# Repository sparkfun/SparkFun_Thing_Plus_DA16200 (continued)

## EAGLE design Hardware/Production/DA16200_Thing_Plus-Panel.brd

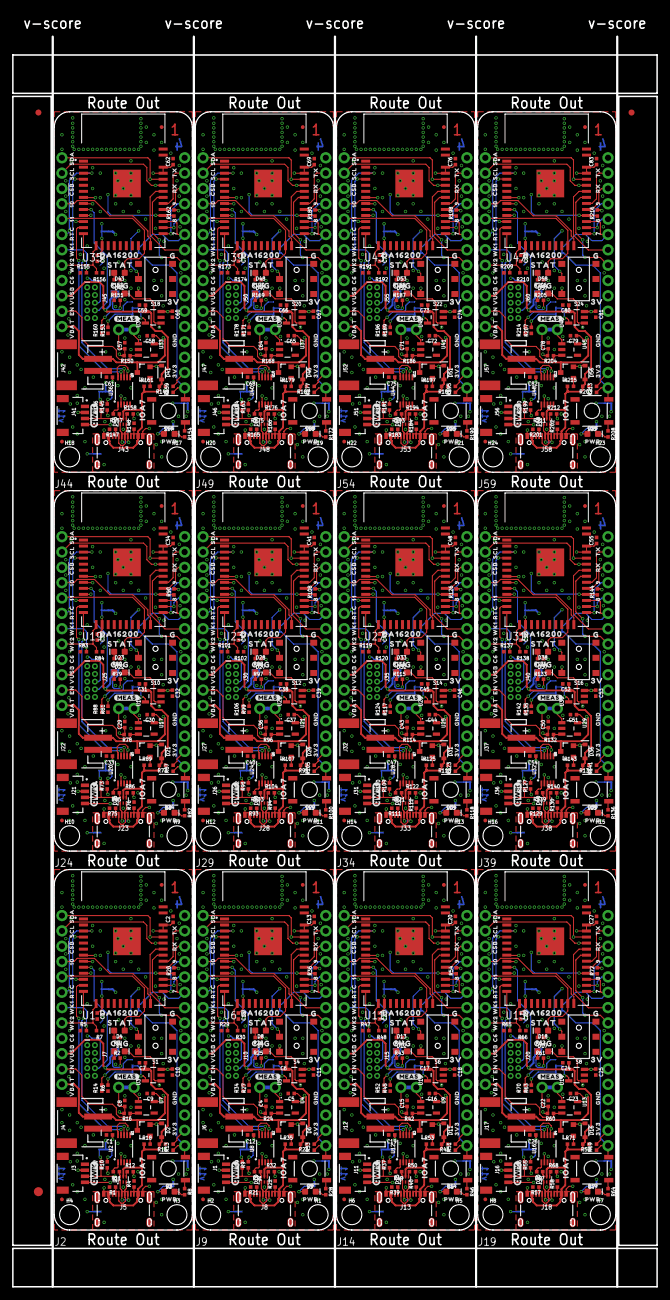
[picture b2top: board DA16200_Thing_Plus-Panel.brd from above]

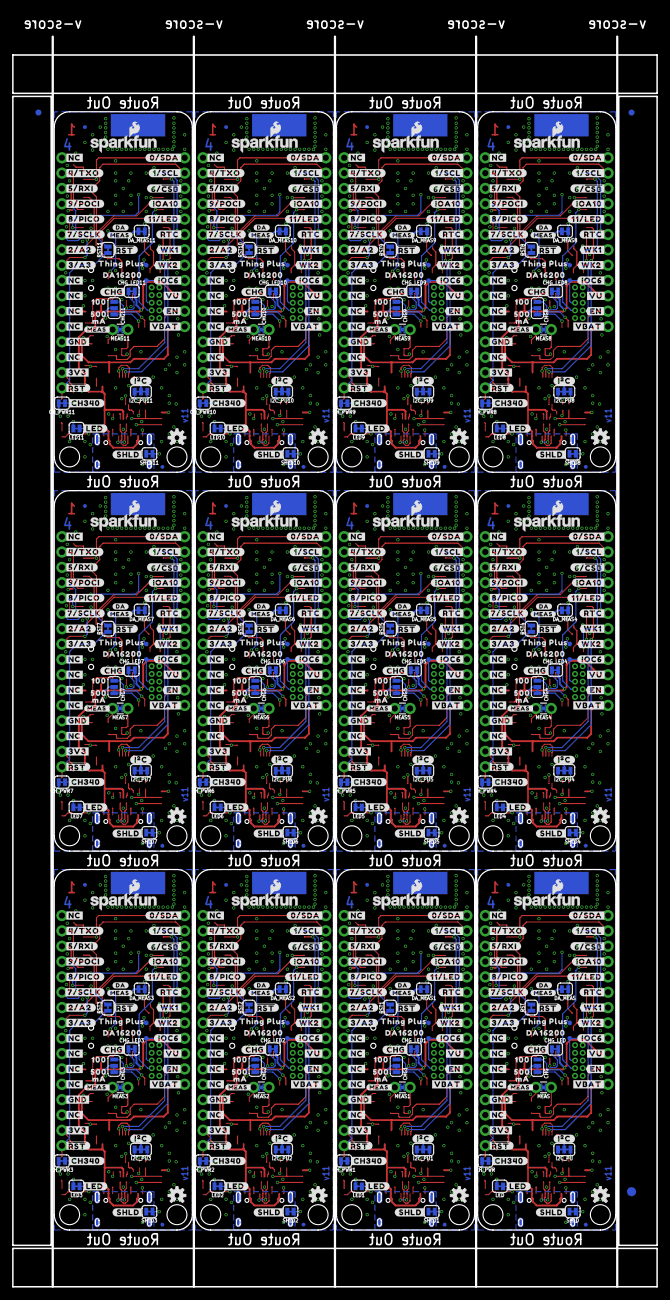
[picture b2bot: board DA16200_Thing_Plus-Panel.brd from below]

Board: 4 copper layers, 106.7 x 207.0 mm, 1578 parts (687 on the bottom side), 636 nets.

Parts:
C1, C2, C3, C12, C13, C14, C19, C20, C21, C26, C27, C28, C33, C34, C35, C40, C41, C42, C47, C48, C49, C54, C55, C56, C61, C62, C63, C68, C69, C70, C75, C76, C77, C82, C83, C84: 0.1uF; 0402-TIGHT
C4, C8, C15, C22, C29, C36, C43, C50, C57, C64, C71, C78: 1.0uF; 0402-TIGHT
C5, C9, C16, C23, C30, C37, C44, C51, C58, C65, C72, C79: 2.2uF; 0402-TIGHT
C6, C7, C10, C11, C17, C18, C24, C25, C31, C32, C38, C39, C45, C46, C52, C53, C59, C60, C66, C67, C73, C74, C80, C81: 4.7uF; 0402-TIGHT
CHG, CHG1, CHG2, CHG3, CHG4, CHG5, CHG6, CHG7, CHG8, CHG9, CHG10, CHG11: JUMPER-SMT_3_1-NC_TRACE_SILK; SMT-JUMPER_3_1-NC_TRACE_SILK
CHG_LED, CHG_LED1, CHG_LED2, CHG_LED3, CHG_LED4, CHG_LED5, CHG_LED6, CHG_LED7, CHG_LED8, CHG_LED9, CHG_LED10, CHG_LED11: JUMPER-SMT_2_NC_TRACE_SILK; SMT-JUMPER_2_NC_TRACE_SILK
CH_PWR, CH_PWR1, CH_PWR2, CH_PWR3, CH_PWR4, CH_PWR5, CH_PWR6, CH_PWR7, CH_PWR8, CH_PWR9, CH_PWR10, CH_PWR11: JUMPER-SMT_2_NC_TRACE_SILK; SMT-JUMPER_2_NC_TRACE_SILK
D1, D7, D12, D17, D22, D27, D32, D37, D42, D47, D52, D57: Yellow; LED-0603
D2, D6, D11, D16, D21, D26, D31, D36, D41, D46, D51, D56: 1A/23V/620mV; SOD-323
D3, D9, D14, D19, D24, D29, D34, D39, D44, D49, D54, D59: RED; LED-0603
D4, D8, D13, D18, D23, D28, D33, D38, D43, D48, D53, D58: BLUE; LED-0603
D5, D10, D15, D20, D25, D30, D35, D40, D45, D50, D55, D60: PRTR5V0U2F; SOT886
DA_MEAS, DA_MEAS1, DA_MEAS2, DA_MEAS3, DA_MEAS4, DA_MEAS5, DA_MEAS6, DA_MEAS7, DA_MEAS8, DA_MEAS9, DA_MEAS10, DA_MEAS11: JUMPER-SMT_2_NC_TRACE_SILK; SMT-JUMPER_2_NC_TRACE_SILK
E$1, E$2, E$3, E$4: FIDUCIAL-1X2
E$5, E$6: FIDUCIAL-1.5X3
FD1, FD2, FD3, FD4, FD5, FD6, FD7, FD8, FD9, FD10, FD11, FD12, FD13, FD14, FD15, FD16, FD17, FD18, FD19, FD20, FD21, FD22, FD23, FD24, FD25, FD26, FD27, FD28, FD29, FD30, FD31, FD32, FD33, FD34, FD35, FD36, FD37, FD38, FD39, FD40, FD41, FD42, FD43, FD44, FD45, FD46, FD47, FD48: FIDUCIALUFIDUCIAL; FIDUCIAL-MICRO
GPIOC1, GPIOC2, GPIOC3, GPIOC4, GPIOC5, GPIOC6, GPIOC7, GPIOC8, GPIOC9, GPIOC10, GPIOC11, GPIOC12: TEST-POINT3; PAD.03X.03
H1, H2, H3, H4, H5, H6, H7, H8, H9, H10, H11, H12, H13, H14, H15, H16, H17, H18, H19, H20, H21, H22, H23, H24: STAND-OFF
I2C_PU, I2C_PU1, I2C_PU2, I2C_PU3, I2C_PU4, I2C_PU5, I2C_PU6, I2C_PU7, I2C_PU8, I2C_PU9, I2C_PU10, I2C_PU11: JUMPER-SMT_3_2-NC_TRACE_SILK; SMT-JUMPER_3_2-NC_TRACE_SILK
J1, J3, J11, J16, J21, J26, J31, J36, J41, J46, J51, J56: Qwiic; JST04_1MM_RA
J2, J9, J14, J19, J24, J29, J34, J39, J44, J49, J54, J59: THING_PLUS
J4, J6, J12, J17, J22, J27, J32, J37, J42, J47, J52, J57: JST-2-SMD
J5, J8, J13, J18, J23, J28, J33, J38, J43, J48, J53, J58: USB C; USB-C-16P-4LAYER-ISOLATED
J7, J10, J15, J20, J25, J30, J35, J40, J45, J50, J55, J60: CORTEX_JTAG_DEBUG_PTH_NS; 2X5-PTH-1.27MM-NO_SILK
LED, LED1, LED2, LED3, LED4, LED5, LED6, LED7, LED8, LED9, LED10, LED11: JUMPER-SMT_2_NC_TRACE_SILK; SMT-JUMPER_2_NC_TRACE_SILK
LOGO1, LOGO3, LOGO5, LOGO7, LOGO9, LOGO11, LOGO13, LOGO15, LOGO17, LOGO19, LOGO21, LOGO23: OSHW-LOGOS; OSHW-LOGO-S
LOGO2, LOGO4, LOGO6, LOGO8, LOGO10, LOGO12, LOGO14, LOGO16, LOGO18, LOGO20, LOGO22, LOGO24: SFE_LOGO_NAME_FLAME.1_INCH; SFE_LOGO_NAME_FLAME_.1
MEAS, MEAS1, MEAS2, MEAS3, MEAS4, MEAS5, MEAS6, MEAS7, MEAS8, MEAS9, MEAS10, MEAS11: JUMPER-COMBO_2_NC_TRACE; COMBO-JUMPER_2_NC_TRACE
Q1, Q2, Q3, Q4, Q5, Q6, Q7, Q8, Q9, Q10, Q11, Q12: 20V/4.2A/52mΩ/1.4W; SOT23-3
R1, R4, R21, R22, R39, R40, R57, R58, R75, R76, R93, R94, R111, R112, R129, R130, R147, R148, R165, R166, R183, R184, R201, R202: 5.1k; 0402-TIGHT
R2, R3, R8, R25, R26, R28, R43, R44, R46, R61, R62, R64, R79, R80, R82, R97, R98, R100, R115, R116, R118, R133, R134, R136, R151, R152, R154, R169, R170, R172, R187, R188, R190, R205, R206, R208: 1k; 0402-TIGHT
R5, R7, R29, R30, R47, R48, R65, R66, R83, R84, R101, R102, R119, R120, R137, R138, R155, R156, R173, R174, R191, R192, R209, R210: 4.7k; 0402-TIGHT
R6, R27, R45, R63, R81, R99, R117, R135, R153, R171, R189, R207: 2.0K; 0402-TIGHT
R9, R10, R17, R19, R37, R38, R55, R56, R73, R74, R91, R92, R109, R110, R127, R128, R145, R146, R163, R164, R181, R182, R199, R200: 2.2k; 0402-TIGHT
R11, R12, R31, R32, R49, R50, R67, R68, R85, R86, R103, R104, R121, R122, R139, R140, R157, R158, R175, R176, R193, R194, R211, R212: 27; 0402-TIGHT
R13, R14, R15, R16, R20, R23, R24, R33, R34, R36, R41, R42, R51, R52, R54, R59, R60, R69, R70, R72, R77, R78, R87, R88, R90, R95, R96, R105, R106, R108, R113, R114, R123, R124, R126, R131, R132, R141, R142, R144, R149, R150, R159, R160, R162, R167, R168, R177, R178, R180, R185, R186, R195, R196, R198, R203, R204, R213, R214, R216: 10k; 0402-TIGHT
R18, R35, R53, R71, R89, R107, R125, R143, R161, R179, R197, R215: 100; 0402-TIGHT
RST, RST1, RST2, RST3, RST4, RST5, RST6, RST7, RST8, RST9, RST10, RST11: JUMPER-SMT_2_NC_TRACE_SILK; SMT-JUMPER_2_NC_TRACE_SILK
S1, S4, S6, S8, S10, S12, S14, S16, S18, S20, S22, S24: SWITCH_DPDT_SMD_AYZ0202
S2, S3, S5, S7, S9, S11, S13, S15, S17, S19, S21, S23: MOMENTARY-SWITCH-SPST-SMD-5.2MM-TALL; TACTILE_SWITCH_SMD_5.2MM
SHLD, SHLD1, SHLD2, SHLD3, SHLD4, SHLD5, SHLD6, SHLD7, SHLD8, SHLD9, SHLD10, SHLD11: JUMPER-SMT_2_NC_TRACE_SILK; SMT-JUMPER_2_NC_TRACE_SILK
TMS, TMS1, TMS2, TMS3, TMS4, TMS5, TMS6, TMS7, TMS8, TMS9, TMS10, TMS11: TEST-POINT3; PAD.03X.03
U1, U6, U11, U15, U19, U23, U27, U31, U35, U39, U43, U47: DA16200MOD; XCVR_DA16200MOD-AAC4WA32
U2, U8, U12, U16, U20, U24, U28, U32, U36, U40, U44, U48: CH340E_MSOP10; MSOP10
U3, U5, U10, U14, U18, U22, U26, U30, U34, U38, U42, U46: MCP73831; SOT23-5
U4, U7, U9, U13, U17, U21, U25, U29, U33, U37, U41, U45: XC6222B331MR-G; SOT23-5
U$1, U$86, U$156, U$226, U$296, U$366, U$436, U$506, U$576, U$646, U$716, U$786: STAT0
U$2, U$87, U$157, U$227, U$297, U$367, U$437, U$507, U$577, U$647, U$717, U$787: CHG0
U$3, U$90, U$160, U$230, U$300, U$370, U$440, U$510, U$580, U$650, U$720, U$790: #MEAS_#0
U$4, U$91, U$161, U$231, U$301, U$371, U$441, U$511, U$581, U$651, U$721, U$791: G0
U$5, U$43, U$88, U$140, U$158, U$210, U$228, U$280, U$298, U$350, U$368, U$420, U$438, U$490, U$508, U$560, U$578, U$630, U$648, U$700, U$718, U$770, U$788, U$840: ##RST##0
U$6, U$94, U$164, U$234, U$304, U$374, U$444, U$514, U$584, U$654, U$724, U$794: #VU#0
U$7, U$129, U$199, U$269, U$339, U$409, U$479, U$549, U$619, U$689, U$759, U$829: #IOA10#0
U$8, U$29, U$89, U$138, U$159, U$208, U$229, U$278, U$299, U$348, U$369, U$418, U$439, U$488, U$509, U$558, U$579, U$628, U$649, U$698, U$719, U$768, U$789, U$838: #MEAS#0
U$9, U$92, U$162, U$232, U$302, U$372, U$442, U$512, U$582, U$652, U$722, U$792: 3V0
U$10, U$123, U$193, U$263, U$333, U$403, U$473, U$543, U$613, U$683, U$753, U$823: #CH340#0
U$11, U$124, U$194, U$264, U$334, U$404, U$474, U$544, U$614, U$684, U$754, U$824: #0#SDA#0
U$12, U$125, U$195, U$265, U$335, U$405, U$475, U$545, U$615, U$685, U$755, U$825: #1#SCL#0
U$13, U$93, U$163, U$233, U$303, U$373, U$443, U$513, U$583, U$653, U$723, U$793: IOA7_0
U$14, U$15, U$18, U$19, U$20, U$40, U$95, U$96, U$97, U$98, U$99, U$114, U$165, U$166, U$167, U$168, U$169, U$184, U$235, U$236, U$237, U$238, U$239, U$254, U$305, U$306, U$307, U$308, U$309, U$324, U$375, U$376, U$377, U$378, U$379, U$394, U$445, U$446, U$447, U$448, U$449, U$464, U$515, U$516, U$517, U$518, U$519, U$534, U$585, U$586, U$587, U$588, U$589, U$604, U$655, U$656, U$657, U$658, U$659, U$674, U$725, U$726, U$727, U$728, U$729, U$744, U$795, U$796, U$797, U$798, U$799, U$814: #NC#0
U$16, U$46, U$142, U$212, U$282, U$352, U$422, U$492, U$562, U$632, U$702, U$772: PWR0
U$17, U$137, U$207, U$277, U$347, U$417, U$487, U$557, U$627, U$697, U$767, U$837: #DA#0
U$21, U$100, U$170, U$240, U$310, U$380, U$450, U$520, U$590, U$660, U$730, U$800: 5000
U$22, U$101, U$171, U$241, U$311, U$381, U$451, U$521, U$591, U$661, U$731, U$801: 1000
U$23, U$102, U$172, U$242, U$312, U$382, U$452, U$522, U$592, U$662, U$732, U$802: MA0
U$24, U$103, U$173, U$243, U$313, U$383, U$453, U$523, U$593, U$663, U$733, U$803: SDA0
U$25, U$104, U$174, U$244, U$314, U$384, U$454, U$524, U$594, U$664, U$734, U$804: SCL0
U$26, U$105, U$175, U$245, U$315, U$385, U$455, U$525, U$595, U$665, U$735, U$805: #CSB#0
U$27, U$130, U$200, U$270, U$340, U$410, U$480, U$550, U$620, U$690, U$760, U$830: #4#TXO#0
U$28, U$113, U$183, U$253, U$323, U$393, U$463, U$533, U$603, U$673, U$743, U$813: 110
U$30, U$139, U$209, U$279, U$349, U$419, U$489, U$559, U$629, U$699, U$769, U$839: #VBAT#0
U$31, U$64, U$141, U$211, U$281, U$351, U$421, U$491, U$561, U$631, U$701, U$771: QWIIC_4MM
U$32, U$106, U$176, U$246, U$316, U$386, U$456, U$526, U$596, U$666, U$736, U$806: 100
U$33, U$107, U$177, U$247, U$317, U$387, U$457, U$527, U$597, U$667, U$737, U$807: RTC0
U$34, U$108, U$178, U$248, U$318, U$388, U$458, U$528, U$598, U$668, U$738, U$808: WK10
U$35, U$109, U$179, U$249, U$319, U$389, U$459, U$529, U$599, U$669, U$739, U$809: WK20
U$36, U$131, U$201, U$271, U$341, U$411, U$481, U$551, U$621, U$691, U$761, U$831: #5#RXI#0
U$37, U$110, U$180, U$250, U$320, U$390, U$460, U$530, U$600, U$670, U$740, U$810: EN0
U$38, U$111, U$181, U$251, U$321, U$391, U$461, U$531, U$601, U$671, U$741, U$811: VUSB0
U$39, U$112, U$182, U$252, U$322, U$392, U$462, U$532, U$602, U$672, U$742, U$812: VBAT0
U$41, U$115, U$185, U$255, U$325, U$395, U$465, U$535, U$605, U$675, U$745, U$815: TX0
U$42, U$116, U$186, U$256, U$326, U$396, U$466, U$536, U$606, U$676, U$746, U$816: RX0
U$44, U$117, U$187, U$257, U$327, U$397, U$467, U$537, U$607, U$677, U$747, U$817: 90
U$45, U$118, U$188, U$258, U$328, U$398, U$468, U$538, U$608, U$678, U$748, U$818: 80
U$47, U$119, U$189, U$259, U$329, U$399, U$469, U$539, U$609, U$679, U$749, U$819: 70
U$48, U$50, U$143, U$213, U$283, U$353, U$423, U$493, U$563, U$633, U$703, U$773: #GND#0
U$49, U$51, U$144, U$214, U$284, U$354, U$424, U$494, U$564, U$634, U$704, U$774: #3V3#0
U$52, U$53, U$145, U$215, U$285, U$355, U$425, U$495, U$565, U$635, U$705, U$775: #EN#0
U$54, U$60, U$146, U$216, U$286, U$356, U$426, U$496, U$566, U$636, U$706, U$776: #IOC6#0
U$55, U$120, U$190, U$260, U$330, U$400, U$470, U$540, U$610, U$680, U$750, U$820: GND0
U$56, U$75, U$150, U$220, U$290, U$360, U$430, U$500, U$570, U$640, U$710, U$780: THING_PLUS0
U$57, U$121, U$191, U$261, U$331, U$401, U$471, U$541, U$611, U$681, U$751, U$821: 3V30
U$58, U$71, U$147, U$217, U$287, U$357, U$427, U$497, U$567, U$637, U$707, U$777: #WK2#0
U$59, U$122, U$192, U$262, U$332, U$402, U$472, U$542, U$612, U$682, U$752, U$822: #CHG#0
U$61, U$72, U$148, U$218, U$288, U$358, U$428, U$498, U$568, U$638, U$708, U$778: #WK1#0
U$62, U$126, U$196, U$266, U$336, U$406, U$476, U$546, U$616, U$686, U$756, U$826: #6##CSB##0
U$63, U$127, U$197, U$267, U$337, U$407, U$477, U$547, U$617, U$687, U$757, U$827: #11#LED#0
U$65, U$128, U$198, U$268, U$338, U$408, U$478, U$548, U$618, U$688, U$758, U$828: C60
U$66, U$132, U$202, U$272, U$342, U$412, U$482, U$552, U$622, U$692, U$762, U$832: #9#POCI#0
U$67, U$133, U$203, U$273, U$343, U$413, U$483, U$553, U$623, U$693, U$763, U$833: #8#PICO#0
U$68, U$134, U$204, U$274, U$344, U$414, U$484, U$554, U$624, U$694, U$764, U$834: #7#SCLK#0
U$69, U$135, U$205, U$275, U$345, U$415, U$485, U$555, U$625, U$695, U$765, U$835: #2#A2#0
U$70, U$136, U$206, U$276, U$346, U$416, U$486, U$556, U$626, U$696, U$766, U$836: #3#A3#0
U$73, U$74, U$149, U$219, U$289, U$359, U$429, U$499, U$569, U$639, U$709, U$779: #RTC#0
U$76, U$77, U$80, U$81, U$151, U$152, U$221, U$222, U$291, U$292, U$361, U$362, U$431, U$432, U$501, U$502, U$571, U$572, U$641, U$642, U$711, U$712, U$781, U$782: DA162000
U$78, U$82, U$153, U$223, U$293, U$363, U$433, U$503, U$573, U$643, U$713, U$783: #I�C#0
U$79, U$84, U$154, U$224, U$294, U$364, U$434, U$504, U$574, U$644, U$714, U$784: #LED#0
U$83, U$85, U$155, U$225, U$295, U$365, U$435, U$505, U$575, U$645, U$715, U$785: #SHLD#0

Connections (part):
3.3V: C1.1, C9.1, CH_PWR.2, DA_MEAS.2, I2C_PU.2, J2.27, J3.2, J7.1, LED.2, R13.2, R20.2, S1.1, U7.5
3.3V1: C5.1, C12.1, CH_PWR1.2, DA_MEAS1.2, I2C_PU1.2, J1.2, J9.27, J10.1, LED1.2, R33.2, R36.2, S4.1, U4.5
3.3V2: C16.1, C19.1, CH_PWR2.2, DA_MEAS2.2, I2C_PU2.2, J11.2, J14.27, J15.1, LED2.2, R51.2, R54.2, S6.1, U9.5
3.3V3: C23.1, C26.1, CH_PWR3.2, DA_MEAS3.2, I2C_PU3.2, J16.2, J19.27, J20.1, LED3.2, R69.2, R72.2, S8.1, U13.5
3.3V4: C30.1, C33.1, CH_PWR4.2, DA_MEAS4.2, I2C_PU4.2, J21.2, J24.27, J25.1, LED4.2, R87.2, R90.2, S10.1, U17.5
3.3V5: C37.1, C40.1, CH_PWR5.2, DA_MEAS5.2, I2C_PU5.2, J26.2, J29.27, J30.1, LED5.2, R105.2, R108.2, S12.1, U21.5
3.3V6: C44.1, C47.1, CH_PWR6.2, DA_MEAS6.2, I2C_PU6.2, J31.2, J34.27, J35.1, LED6.2, R123.2, R126.2, S14.1, U25.5
3.3V7: C51.1, C54.1, CH_PWR7.2, DA_MEAS7.2, I2C_PU7.2, J36.2, J39.27, J40.1, LED7.2, R141.2, R144.2, S16.1, U29.5
3.3V8: C58.1, C61.1, CH_PWR8.2, DA_MEAS8.2, I2C_PU8.2, J41.2, J44.27, J45.1, LED8.2, R159.2, R162.2, S18.1, U33.5
3.3V9: C65.1, C68.1, CH_PWR9.2, DA_MEAS9.2, I2C_PU9.2, J46.2, J49.27, J50.1, LED9.2, R177.2, R180.2, S20.1, U37.5
3.3V10: C72.1, C75.1, CH_PWR10.2, DA_MEAS10.2, I2C_PU10.2, J51.2, J54.27, J55.1, LED10.2, R195.2, R198.2, S22.1, U41.5
3.3V11: C79.1, C82.1, CH_PWR11.2, DA_MEAS11.2, I2C_PU11.2, J56.2, J59.27, J60.1, LED11.2, R213.2, R216.2, S24.1, U45.5
!RESET!: J2.28, R13.1, RST.1, S2.3
!RESET!1: J9.28, R33.1, RST1.1, S3.3
!RESET!2: J14.28, R51.1, RST2.1, S5.3
!RESET!3: J19.28, R69.1, RST3.1, S7.3
!RESET!4: J24.28, R87.1, RST4.1, S9.3
!RESET!5: J29.28, R105.1, RST5.1, S11.3
!RESET!6: J34.28, R123.1, RST6.1, S13.3
!RESET!7: J39.28, R141.1, RST7.1, S15.3
!RESET!8: J44.28, R159.1, RST8.1, S17.3
!RESET!9: J49.28, R177.1, RST9.1, S19.3
!RESET!10: J54.28, R195.1, RST10.1, S21.3
!RESET!11: J59.28, R213.1, RST11.1, S23.3
!RESET!/SPI_CLK: J2.18, RST.2, U1.26
!RESET!/SPI_CLK1: J9.18, RST1.2, U6.26
!RESET!/SPI_CLK2: J14.18, RST2.2, U11.26
!RESET!/SPI_CLK3: J19.18, RST3.2, U15.26
!RESET!/SPI_CLK4: J24.18, RST4.2, U19.26
!RESET!/SPI_CLK5: J29.18, RST5.2, U23.26
!RESET!/SPI_CLK6: J34.18, RST6.2, U27.26
!RESET!/SPI_CLK7: J39.18, RST7.2, U31.26
!RESET!/SPI_CLK8: J44.18, RST8.2, U35.26
!RESET!/SPI_CLK9: J49.18, RST9.2, U39.26
!RESET!/SPI_CLK10: J54.18, RST10.2, U43.26
!RESET!/SPI_CLK11: J59.18, RST11.2, U47.26
A_CH1: J9.19, U6.31
A_CH2: J2.19, U1.31
A_CH3: J2.20, U1.30
A_CH4: J9.20, U6.30
A_CH5: J14.19, U11.31
A_CH6: J14.20, U11.30
A_CH7: J19.19, U15.31
A_CH8: J19.20, U15.30
A_CH9: J24.19, U19.31
A_CH10: J24.20, U19.30
A_CH11: J29.19, U23.31
A_CH12: J29.20, U23.30
A_CH13: J34.19, U27.31
A_CH14: J34.20, U27.30
A_CH15: J39.19, U31.31
A_CH16: J39.20, U31.30
A_CH17: J44.19, U35.31
A_CH18: J44.20, U35.30
A_CH19: J49.19, U39.31
A_CH20: J49.20, U39.30
A_CH21: J54.19, U43.31
A_CH22: J54.20, U43.30
A_CH23: J59.19, U47.31
A_CH24: J59.20, U47.30
EN: J2.11, R16.1, U7.3
EN1: J9.11, R24.1, U4.3
EN2: J14.11, R42.1, U9.3
EN3: J19.11, R60.1, U13.3
EN4: J24.11, R78.1, U17.3
EN5: J29.11, R96.1, U21.3
EN6: J34.11, R114.1, U25.3
EN7: J39.11, R132.1, U29.3
EN8: J44.11, R150.1, U33.3
EN9: J49.11, R168.1, U37.3
EN10: J54.11, R186.1, U41.3
EN11: J59.11, R204.1, U45.3
GND: C1.2, C2.2, C3.2, C7.2, C8.2, C9.2, C10.2, D5.2, J2.25, J3.1, J4.1, J5.GND, J5.GND2, J7.3, J7.5, J7.9, R1.2, R3.1, R4.2, R5.1, R6.1, R7.1, R8.1, R14.1, R15.1, S1.3, S2.1, SHLD.1, U1.2, U1.ANT_GND, U1.GND, U2.3, U3.2, U7.2
GND1: C4.2, C5.2, C6.2, C11.2, C12.2, C13.2, C14.2, D10.2, J1.1, J6.1, J8.GND, J8.GND2, J9.25, J10.3, J10.5, J10.9, R21.2, R22.2, R23.1, R26.1, R27.1, R28.1, R29.1, R30.1, R34.1, S3.1, S4.3, SHLD1.1, U4.2, U5.2, U6.2, U6.ANT_GND, U6.GND, U8.3
GND2: C15.2, C16.2, C17.2, C18.2, C19.2, C20.2, C21.2, D15.2, J11.1, J12.1, J13.GND, J13.GND2, J14.25, J15.3, J15.5, J15.9, R39.2, R40.2, R41.1, R44.1, R45.1, R46.1, R47.1, R48.1, R52.1, S5.1, S6.3, SHLD2.1, U9.2, U10.2, U11.2, U11.ANT_GND, U11.GND, U12.3
GND3: C22.2, C23.2, C24.2, C25.2, C26.2, C27.2, C28.2, D20.2, J16.1, J17.1, J18.GND, J18.GND2, J19.25, J20.3, J20.5, J20.9, R57.2, R58.2, R59.1, R62.1, R63.1, R64.1, R65.1, R66.1, R70.1, S7.1, S8.3, SHLD3.1, U13.2, U14.2, U15.2, U15.ANT_GND, U15.GND, U16.3
GND4: C29.2, C30.2, C31.2, C32.2, C33.2, C34.2, C35.2, D25.2, J21.1, J22.1, J23.GND, J23.GND2, J24.25, J25.3, J25.5, J25.9, R75.2, R76.2, R77.1, R80.1, R81.1, R82.1, R83.1, R84.1, R88.1, S9.1, S10.3, SHLD4.1, U17.2, U18.2, U19.2, U19.ANT_GND, U19.GND, U20.3
GND5: C36.2, C37.2, C38.2, C39.2, C40.2, C41.2, C42.2, D30.2, J26.1, J27.1, J28.GND, J28.GND2, J29.25, J30.3, J30.5, J30.9, R93.2, R94.2, R95.1, R98.1, R99.1, R100.1, R101.1, R102.1, R106.1, S11.1, S12.3, SHLD5.1, U21.2, U22.2, U23.2, U23.ANT_GND, U23.GND, U24.3
GND6: C43.2, C44.2, C45.2, C46.2, C47.2, C48.2, C49.2, D35.2, J31.1, J32.1, J33.GND, J33.GND2, J34.25, J35.3, J35.5, J35.9, R111.2, R112.2, R113.1, R116.1, R117.1, R118.1, R119.1, R120.1, R124.1, S13.1, S14.3, SHLD6.1, U25.2, U26.2, U27.2, U27.ANT_GND, U27.GND, U28.3
GND7: C50.2, C51.2, C52.2, C53.2, C54.2, C55.2, C56.2, D40.2, J36.1, J37.1, J38.GND, J38.GND2, J39.25, J40.3, J40.5, J40.9, R129.2, R130.2, R131.1, R134.1, R135.1, R136.1, R137.1, R138.1, R142.1, S15.1, S16.3, SHLD7.1, U29.2, U30.2, U31.2, U31.ANT_GND, U31.GND, U32.3
GND8: C57.2, C58.2, C59.2, C60.2, C61.2, C62.2, C63.2, D45.2, J41.1, J42.1, J43.GND, J43.GND2, J44.25, J45.3, J45.5, J45.9, R147.2, R148.2, R149.1, R152.1, R153.1, R154.1, R155.1, R156.1, R160.1, S17.1, S18.3, SHLD8.1, U33.2, U34.2, U35.2, U35.ANT_GND, U35.GND, U36.3
GND9: C64.2, C65.2, C66.2, C67.2, C68.2, C69.2, C70.2, D50.2, J46.1, J47.1, J48.GND, J48.GND2, J49.25, J50.3, J50.5, J50.9, R165.2, R166.2, R167.1, R170.1, R171.1, R172.1, R173.1, R174.1, R178.1, S19.1, S20.3, SHLD9.1, U37.2, U38.2, U39.2, U39.ANT_GND, U39.GND, U40.3
GND10: C71.2, C72.2, C73.2, C74.2, C75.2, C76.2, C77.2, D55.2, J51.1, J52.1, J53.GND, J53.GND2, J54.25, J55.3, J55.5, J55.9, R183.2, R184.2, R185.1, R188.1, R189.1, R190.1, R191.1, R192.1, R196.1, S21.1, S22.3, SHLD10.1, U41.2, U42.2, U43.2, U43.ANT_GND, U43.GND, U44.3
GND11: C78.2, C79.2, C80.2, C81.2, C82.2, C83.2, C84.2, D60.2, J56.1, J57.1, J58.GND, J58.GND2, J59.25, J60.3, J60.5, J60.9, R201.2, R202.2, R203.1, R206.1, R207.1, R208.1, R209.1, R210.1, R214.1, S23.1, S24.3, SHLD11.1, U45.2, U46.2, U47.2, U47.ANT_GND, U47.GND, U48.3
GPIOA1: J9.4, U6.23
GPIOA2: J14.4, U11.23
GPIOA3: J19.4, U15.23
GPIOA4: J24.4, U19.23
GPIOA5: J29.4, U23.23
GPIOA6: J34.4, U27.23
GPIOA7: J39.4, U31.23
GPIOA8: J44.4, U35.23
GPIOA9: J49.4, U39.23
GPIOA10: J2.4, U1.23
GPIOA11: J54.4, U43.23
GPIOA12: J59.4, U47.23
GPIOC1: J9.9, J10.10, U6.11
GPIOC2: GPIOC1.1, J10.6, U6.10
GPIOC3: J10.8, U6.9
GPIOC4: J14.9, J15.10, U11.11
GPIOC5: GPIOC2.1, J15.6, U11.10
GPIOC6: J2.9, J7.10, U1.11
GPIOC7: GPIOC7.1, J7.6, U1.10
GPIOC8: J7.8, U1.9
GPIOC9: J15.8, U11.9
GPIOC10: J19.9, J20.10, U15.11
GPIOC11: GPIOC3.1, J20.6, U15.10
GPIOC12: J20.8, U15.9
GPIOC13: J24.9, J25.10, U19.11
GPIOC14: GPIOC4.1, J25.6, U19.10
GPIOC15: J25.8, U19.9
GPIOC16: J29.9, J30.10, U23.11
GPIOC17: GPIOC5.1, J30.6, U23.10
GPIOC18: J30.8, U23.9
GPIOC19: J34.9, J35.10, U27.11
GPIOC20: GPIOC6.1, J35.6, U27.10
GPIOC21: J35.8, U27.9
GPIOC22: J39.9, J40.10, U31.11
GPIOC23: GPIOC8.1, J40.6, U31.10
GPIOC24: J40.8, U31.9
GPIOC25: J44.9, J45.10, U35.11
GPIOC26: GPIOC9.1, J45.6, U35.10
GPIOC27: J45.8, U35.9
GPIOC28: J49.9, J50.10, U39.11
GPIOC29: GPIOC10.1, J50.6, U39.10
GPIOC30: J50.8, U39.9
GPIOC31: J54.9, J55.10, U43.11
GPIOC32: GPIOC11.1, J55.6, U43.10
GPIOC33: J55.8, U43.9
GPIOC34: J59.9, J60.10, U47.11
GPIOC35: GPIOC12.1, J60.6, U47.10
GPIOC36: J60.8, U47.9
HDR_RTC_WAKE1: J9.8, R30.2, U6.14
HDR_RTC_WAKE2: J2.8, R7.2, U1.14
HDR_RTC_WAKE3: J14.8, R48.2, U11.14
HDR_RTC_WAKE4: J19.8, R66.2, U15.14
HDR_RTC_WAKE5: J24.8, R84.2, U19.14
HDR_RTC_WAKE6: J29.8, R102.2, U23.14
HDR_RTC_WAKE7: J34.8, R120.2, U27.14
HDR_RTC_WAKE8: J39.8, R138.2, U31.14
HDR_RTC_WAKE9: J44.8, R156.2, U35.14
HDR_RTC_WAKE10: J49.8, R174.2, U39.14
HDR_RTC_WAKE11: J54.8, R192.2, U43.14
HDR_RTC_WAKE12: J59.8, R210.2, U47.14
I2C_SCL: J2.2, J3.4, R10.1, U1.32
I2C_SCL1: J1.4, J9.2, R9.1, U6.32
I2C_SCL2: J11.4, J14.2, R37.1, U11.32
I2C_SCL3: J16.4, J19.2, R55.1, U15.32
I2C_SCL4: J21.4, J24.2, R73.1, U19.32
I2C_SCL5: J26.4, J29.2, R91.1, U23.32
I2C_SCL6: J31.4, J34.2, R109.1, U27.32
I2C_SCL7: J36.4, J39.2, R127.1, U31.32
I2C_SCL8: J41.4, J44.2, R145.1, U35.32
I2C_SCL9: J46.4, J49.2, R163.1, U39.32
I2C_SCL10: J51.4, J54.2, R181.1, U43.32
I2C_SCL11: J56.4, J59.2, R199.1, U47.32
I2C_SDA: J2.1, J3.3, R17.1, U1.33
I2C_SDA1: J1.3, J9.1, R19.1, U6.33
I2C_SDA2: J11.3, J14.1, R38.1, U11.33
I2C_SDA3: J16.3, J19.1, R56.1, U15.33
I2C_SDA4: J21.3, J24.1, R74.1, U19.33
I2C_SDA5: J26.3, J29.1, R92.1, U23.33
I2C_SDA6: J31.3, J34.1, R110.1, U27.33
I2C_SDA7: J36.3, J39.1, R128.1, U31.33
I2C_SDA8: J41.3, J44.1, R146.1, U35.33
I2C_SDA9: J46.3, J49.1, R164.1, U39.33
I2C_SDA10: J51.3, J54.1, R182.1, U43.33
I2C_SDA11: J56.3, J59.1, R200.1, U47.33
unnamed: D4.C, R3.2
unnamed: I2C_PU.3, R10.2
unnamed: I2C_PU.1, R17.2
unnamed: D3.A, LED.1
unnamed: D5.1, J5.A6, J5.B6
unnamed: D5.3, J5.A7, J5.B7
unnamed: D3.C, R8.2
unnamed: C2.1, C3.1, DA_MEAS.1, U1.15, U1.34, U1.35
unnamed: D1.C, U3.1
unnamed: CHG.3, R6.2
unnamed: J5.A5, R1.1
unnamed: J5.B5, R4.1
unnamed: D5.6, R11.1
unnamed: CHG.2, U3.5
unnamed: C8.1, D2.C, MEAS.1, MEAS.3, Q1.2, R16.2
unnamed: D5.4, R12.1
unnamed: D1.A, R2.1
unnamed: R11.2, U2.1
unnamed: R12.2, U2.2
unnamed: CHG.1, R14.2
unnamed: Q1.1, R18.2
unnamed: MEAS.2, MEAS.4, U7.1
unnamed: CHG_LED.1, R2.2
unnamed: J5.SHLD1, J5.SHLD2, J5.SHLD3, J5.SHLD4, J5.SHLD5, J5.SHLD6, J5.SHLD7, J5.SHLD8, SHLD.2
unnamed: D7.C, U5.1
unnamed: CH_PWR.1, U2.7, U2.10
unnamed: CHG1.2, U5.5
unnamed: D7.A, R25.1
unnamed: D8.C, R26.2
unnamed: I2C_PU1.3, R9.2
unnamed: I2C_PU1.1, R19.2
unnamed: J8.A5, R21.1
unnamed: J8.B5, R22.1
unnamed: C4.1, D6.C, MEAS1.1, MEAS1.3, Q2.2, R24.2
unnamed: D9.C, R28.2
unnamed: D9.A, LED1.1
unnamed: D10.1, J8.A6, J8.B6
unnamed: D10.3, J8.A7, J8.B7
unnamed: D10.6, R31.1
unnamed: D10.4, R32.1
unnamed: R31.2, U8.1
unnamed: R32.2, U8.2
unnamed: CHG1.3, R27.2
unnamed: CHG1.1, R34.2
unnamed: Q2.1, R35.2
unnamed: J8.SHLD1, J8.SHLD2, J8.SHLD3, J8.SHLD4, J8.SHLD5, J8.SHLD6, J8.SHLD7, J8.SHLD8, SHLD1.2
unnamed: MEAS1.2, MEAS1.4, U4.1
unnamed: CHG_LED1.1, R25.2
unnamed: CH_PWR1.1, U8.7, U8.10
unnamed: C13.1, C14.1, DA_MEAS1.1, U6.15, U6.34, U6.35
unnamed: D12.C, U10.1
unnamed: CHG2.2, U10.5
unnamed: D12.A, R43.1
unnamed: D13.C, R44.2
unnamed: I2C_PU2.3, R37.2
unnamed: I2C_PU2.1, R38.2
unnamed: J13.A5, R39.1
unnamed: J13.B5, R40.1
unnamed: C15.1, D11.C, MEAS2.1, MEAS2.3, Q3.2, R42.2
unnamed: D14.C, R46.2
unnamed: D14.A, LED2.1
unnamed: D15.1, J13.A6, J13.B6
unnamed: D15.3, J13.A7, J13.B7
unnamed: D15.6, R49.1
unnamed: D15.4, R50.1
unnamed: R49.2, U12.1
unnamed: R50.2, U12.2
unnamed: CHG2.3, R45.2
unnamed: CHG2.1, R52.2
unnamed: Q3.1, R53.2
unnamed: J13.SHLD1, J13.SHLD2, J13.SHLD3, J13.SHLD4, J13.SHLD5, J13.SHLD6, J13.SHLD7, J13.SHLD8, SHLD2.2
unnamed: MEAS2.2, MEAS2.4, U9.1
unnamed: CHG_LED2.1, R43.2
unnamed: CH_PWR2.1, U12.7, U12.10
unnamed: C20.1, C21.1, DA_MEAS2.1, U11.15, U11.34, U11.35
unnamed: D17.C, U14.1
unnamed: CHG3.2, U14.5
unnamed: D17.A, R61.1
unnamed: D18.C, R62.2
unnamed: I2C_PU3.3, R55.2
unnamed: I2C_PU3.1, R56.2
unnamed: J18.A5, R57.1
unnamed: J18.B5, R58.1
unnamed: C22.1, D16.C, MEAS3.1, MEAS3.3, Q4.2, R60.2
unnamed: D19.C, R64.2
unnamed: D19.A, LED3.1
unnamed: D20.1, J18.A6, J18.B6
unnamed: D20.3, J18.A7, J18.B7
unnamed: D20.6, R67.1
unnamed: D20.4, R68.1
unnamed: R67.2, U16.1
unnamed: R68.2, U16.2
unnamed: CHG3.3, R63.2
unnamed: CHG3.1, R70.2
unnamed: Q4.1, R71.2
unnamed: J18.SHLD1, J18.SHLD2, J18.SHLD3, J18.SHLD4, J18.SHLD5, J18.SHLD6, J18.SHLD7, J18.SHLD8, SHLD3.2
unnamed: MEAS3.2, MEAS3.4, U13.1
unnamed: CHG_LED3.1, R61.2
unnamed: CH_PWR3.1, U16.7, U16.10
unnamed: C27.1, C28.1, DA_MEAS3.1, U15.15, U15.34, U15.35
unnamed: D22.C, U18.1
unnamed: CHG4.2, U18.5
unnamed: D22.A, R79.1
unnamed: D23.C, R80.2
unnamed: I2C_PU4.3, R73.2
unnamed: I2C_PU4.1, R74.2
unnamed: J23.A5, R75.1
unnamed: J23.B5, R76.1
unnamed: C29.1, D21.C, MEAS4.1, MEAS4.3, Q5.2, R78.2
unnamed: D24.C, R82.2
unnamed: D24.A, LED4.1
unnamed: D25.1, J23.A6, J23.B6
unnamed: D25.3, J23.A7, J23.B7
unnamed: D25.6, R85.1
unnamed: D25.4, R86.1
unnamed: R85.2, U20.1
unnamed: R86.2, U20.2
unnamed: CHG4.3, R81.2
unnamed: CHG4.1, R88.2
unnamed: Q5.1, R89.2
unnamed: J23.SHLD1, J23.SHLD2, J23.SHLD3, J23.SHLD4, J23.SHLD5, J23.SHLD6, J23.SHLD7, J23.SHLD8, SHLD4.2
unnamed: MEAS4.2, MEAS4.4, U17.1
unnamed: CHG_LED4.1, R79.2
unnamed: CH_PWR4.1, U20.7, U20.10
unnamed: C34.1, C35.1, DA_MEAS4.1, U19.15, U19.34, U19.35
unnamed: D27.C, U22.1
unnamed: CHG5.2, U22.5
unnamed: D27.A, R97.1
unnamed: D28.C, R98.2
unnamed: I2C_PU5.3, R91.2
unnamed: I2C_PU5.1, R92.2
unnamed: J28.A5, R93.1
unnamed: J28.B5, R94.1
unnamed: C36.1, D26.C, MEAS5.1, MEAS5.3, Q6.2, R96.2
unnamed: D29.C, R100.2
unnamed: D29.A, LED5.1
unnamed: D30.1, J28.A6, J28.B6
unnamed: D30.3, J28.A7, J28.B7
unnamed: D30.6, R103.1
unnamed: D30.4, R104.1
unnamed: R103.2, U24.1
unnamed: R104.2, U24.2
unnamed: CHG5.3, R99.2
unnamed: CHG5.1, R106.2
unnamed: Q6.1, R107.2
unnamed: J28.SHLD1, J28.SHLD2, J28.SHLD3, J28.SHLD4, J28.SHLD5, J28.SHLD6, J28.SHLD7, J28.SHLD8, SHLD5.2
unnamed: MEAS5.2, MEAS5.4, U21.1
unnamed: CHG_LED5.1, R97.2
unnamed: CH_PWR5.1, U24.7, U24.10
unnamed: C41.1, C42.1, DA_MEAS5.1, U23.15, U23.34, U23.35
unnamed: D32.C, U26.1
unnamed: CHG6.2, U26.5
unnamed: D32.A, R115.1
unnamed: D33.C, R116.2
unnamed: I2C_PU6.3, R109.2
unnamed: I2C_PU6.1, R110.2
unnamed: J33.A5, R111.1
unnamed: J33.B5, R112.1
unnamed: C43.1, D31.C, MEAS6.1, MEAS6.3, Q7.2, R114.2
unnamed: D34.C, R118.2
unnamed: D34.A, LED6.1
unnamed: D35.1, J33.A6, J33.B6
unnamed: D35.3, J33.A7, J33.B7
unnamed: D35.6, R121.1
unnamed: D35.4, R122.1
unnamed: R121.2, U28.1
unnamed: R122.2, U28.2
unnamed: CHG6.3, R117.2
unnamed: CHG6.1, R124.2
unnamed: Q7.1, R125.2
unnamed: J33.SHLD1, J33.SHLD2, J33.SHLD3, J33.SHLD4, J33.SHLD5, J33.SHLD6, J33.SHLD7, J33.SHLD8, SHLD6.2
unnamed: MEAS6.2, MEAS6.4, U25.1
unnamed: CHG_LED6.1, R115.2
unnamed: CH_PWR6.1, U28.7, U28.10
unnamed: C48.1, C49.1, DA_MEAS6.1, U27.15, U27.34, U27.35
unnamed: D37.C, U30.1
unnamed: CHG7.2, U30.5
unnamed: D37.A, R133.1
unnamed: D38.C, R134.2
unnamed: I2C_PU7.3, R127.2
unnamed: I2C_PU7.1, R128.2
unnamed: J38.A5, R129.1
unnamed: J38.B5, R130.1
unnamed: C50.1, D36.C, MEAS7.1, MEAS7.3, Q8.2, R132.2
unnamed: D39.C, R136.2
unnamed: D39.A, LED7.1
unnamed: D40.1, J38.A6, J38.B6
unnamed: D40.3, J38.A7, J38.B7
unnamed: D40.6, R139.1
unnamed: D40.4, R140.1
unnamed: R139.2, U32.1
unnamed: R140.2, U32.2
unnamed: CHG7.3, R135.2
unnamed: CHG7.1, R142.2
unnamed: Q8.1, R143.2
unnamed: J38.SHLD1, J38.SHLD2, J38.SHLD3, J38.SHLD4, J38.SHLD5, J38.SHLD6, J38.SHLD7, J38.SHLD8, SHLD7.2
unnamed: MEAS7.2, MEAS7.4, U29.1
unnamed: CHG_LED7.1, R133.2
unnamed: CH_PWR7.1, U32.7, U32.10
unnamed: C55.1, C56.1, DA_MEAS7.1, U31.15, U31.34, U31.35
unnamed: D42.C, U34.1
unnamed: CHG8.2, U34.5
unnamed: D42.A, R151.1
unnamed: D43.C, R152.2
unnamed: I2C_PU8.3, R145.2
unnamed: I2C_PU8.1, R146.2
unnamed: J43.A5, R147.1
unnamed: J43.B5, R148.1
unnamed: C57.1, D41.C, MEAS8.1, MEAS8.3, Q9.2, R150.2
unnamed: D44.C, R154.2
unnamed: D44.A, LED8.1
unnamed: D45.1, J43.A6, J43.B6
unnamed: D45.3, J43.A7, J43.B7
unnamed: D45.6, R157.1
unnamed: D45.4, R158.1
unnamed: R157.2, U36.1
unnamed: R158.2, U36.2
unnamed: CHG8.3, R153.2
unnamed: CHG8.1, R160.2
unnamed: Q9.1, R161.2
unnamed: J43.SHLD1, J43.SHLD2, J43.SHLD3, J43.SHLD4, J43.SHLD5, J43.SHLD6, J43.SHLD7, J43.SHLD8, SHLD8.2
unnamed: MEAS8.2, MEAS8.4, U33.1
unnamed: CHG_LED8.1, R151.2
unnamed: CH_PWR8.1, U36.7, U36.10
unnamed: C62.1, C63.1, DA_MEAS8.1, U35.15, U35.34, U35.35
unnamed: D47.C, U38.1
unnamed: CHG9.2, U38.5
unnamed: D47.A, R169.1
unnamed: D48.C, R170.2
unnamed: I2C_PU9.3, R163.2
unnamed: I2C_PU9.1, R164.2
unnamed: J48.A5, R165.1
unnamed: J48.B5, R166.1
unnamed: C64.1, D46.C, MEAS9.1, MEAS9.3, Q10.2, R168.2
unnamed: D49.C, R172.2
unnamed: D49.A, LED9.1
unnamed: D50.1, J48.A6, J48.B6
unnamed: D50.3, J48.A7, J48.B7
unnamed: D50.6, R175.1
unnamed: D50.4, R176.1
unnamed: R175.2, U40.1
unnamed: R176.2, U40.2
unnamed: CHG9.3, R171.2
unnamed: CHG9.1, R178.2
unnamed: Q10.1, R179.2
unnamed: J48.SHLD1, J48.SHLD2, J48.SHLD3, J48.SHLD4, J48.SHLD5, J48.SHLD6, J48.SHLD7, J48.SHLD8, SHLD9.2
unnamed: MEAS9.2, MEAS9.4, U37.1
unnamed: CHG_LED9.1, R169.2
unnamed: CH_PWR9.1, U40.7, U40.10
unnamed: C69.1, C70.1, DA_MEAS9.1, U39.15, U39.34, U39.35
unnamed: D52.C, U42.1
unnamed: CHG10.2, U42.5
unnamed: D52.A, R187.1
unnamed: D53.C, R188.2
unnamed: I2C_PU10.3, R181.2
unnamed: I2C_PU10.1, R182.2
unnamed: J53.A5, R183.1
unnamed: J53.B5, R184.1
unnamed: C71.1, D51.C, MEAS10.1, MEAS10.3, Q11.2, R186.2
unnamed: D54.C, R190.2
unnamed: D54.A, LED10.1
unnamed: D55.1, J53.A6, J53.B6
unnamed: D55.3, J53.A7, J53.B7
unnamed: D55.6, R193.1
unnamed: D55.4, R194.1
unnamed: R193.2, U44.1
unnamed: R194.2, U44.2
unnamed: CHG10.3, R189.2
unnamed: CHG10.1, R196.2
unnamed: Q11.1, R197.2
unnamed: J53.SHLD1, J53.SHLD2, J53.SHLD3, J53.SHLD4, J53.SHLD5, J53.SHLD6, J53.SHLD7, J53.SHLD8, SHLD10.2
unnamed: MEAS10.2, MEAS10.4, U41.1
unnamed: CHG_LED10.1, R187.2
unnamed: CH_PWR10.1, U44.7, U44.10
unnamed: C76.1, C77.1, DA_MEAS10.1, U43.15, U43.34, U43.35
unnamed: D57.C, U46.1
unnamed: CHG11.2, U46.5
unnamed: D57.A, R205.1
unnamed: D58.C, R206.2
unnamed: I2C_PU11.3, R199.2
unnamed: I2C_PU11.1, R200.2
unnamed: J58.A5, R201.1
unnamed: J58.B5, R202.1
unnamed: C78.1, D56.C, MEAS11.1, MEAS11.3, Q12.2, R204.2
unnamed: D59.C, R208.2
unnamed: D59.A, LED11.1
unnamed: D60.1, J58.A6, J58.B6
unnamed: D60.3, J58.A7, J58.B7
unnamed: D60.6, R211.1
unnamed: D60.4, R212.1
unnamed: R211.2, U48.1
unnamed: R212.2, U48.2
unnamed: CHG11.3, R207.2
unnamed: CHG11.1, R214.2
unnamed: Q12.1, R215.2
unnamed: J58.SHLD1, J58.SHLD2, J58.SHLD3, J58.SHLD4, J58.SHLD5, J58.SHLD6, J58.SHLD7, J58.SHLD8, SHLD11.2
unnamed: MEAS11.2, MEAS11.4, U45.1
unnamed: CHG_LED11.1, R205.2
unnamed: CH_PWR11.1, U48.7, U48.10
unnamed: C83.1, C84.1, DA_MEAS11.1, U47.15, U47.34, U47.35
RTC_PWR_KEY: J2.6, S1.2, U1.3
RTC_PWR_KEY1: J9.6, S4.2, U6.3
RTC_PWR_KEY2: J14.6, S6.2, U11.3
RTC_PWR_KEY3: J19.6, S8.2, U15.3
RTC_PWR_KEY4: J24.6, S10.2, U19.3
RTC_PWR_KEY5: J29.6, S12.2, U23.3
RTC_PWR_KEY6: J34.6, S14.2, U27.3
RTC_PWR_KEY7: J39.6, S16.2, U31.3
RTC_PWR_KEY8: J44.6, S18.2, U35.3
RTC_PWR_KEY9: J49.6, S20.2, U39.3
RTC_PWR_KEY10: J54.6, S22.2, U43.3
RTC_PWR_KEY11: J59.6, S24.2, U47.3
RTC_WAKE1: J2.7, R5.2, U1.4
RTC_WAKE2: J9.7, R29.2, U6.4
RTC_WAKE3: J14.7, R47.2, U11.4
RTC_WAKE4: J19.7, R65.2, U15.4
RTC_WAKE5: J24.7, R83.2, U19.4
RTC_WAKE6: J29.7, R101.2, U23.4
RTC_WAKE7: J34.7, R119.2, U27.4
RTC_WAKE8: J39.7, R137.2, U31.4
RTC_WAKE9: J44.7, R155.2, U35.4
RTC_WAKE10: J49.7, R173.2, U39.4
RTC_WAKE11: J54.7, R191.2, U43.4
RTC_WAKE12: J59.7, R209.2, U47.4
SPI_CSB: J2.3, R20.1, U1.27
SPI_CSB1: J9.3, R36.1, U6.27
SPI_CSB2: J14.3, R54.1, U11.27
SPI_CSB3: J19.3, R72.1, U15.27
SPI_CSB4: J24.3, R90.1, U19.27
SPI_CSB5: J29.3, R108.1, U23.27
SPI_CSB6: J34.3, R126.1, U27.27
SPI_CSB7: J39.3, R144.1, U31.27
SPI_CSB8: J44.3, R162.1, U35.27
SPI_CSB9: J49.3, R180.1, U39.27
SPI_CSB10: J54.3, R198.1, U43.27
SPI_CSB11: J59.3, R216.1, U47.27
SPI_PICO: J2.17, U1.25
SPI_PICO1: J9.17, U6.25
SPI_PICO2: J14.17, U11.25
SPI_PICO3: J19.17, U15.25
SPI_PICO4: J24.17, U19.25
SPI_PICO5: J29.17, U23.25
SPI_PICO6: J34.17, U27.25
SPI_PICO7: J39.17, U31.25
SPI_PICO8: J44.17, U35.25
SPI_PICO9: J49.17, U39.25
SPI_PICO10: J54.17, U43.25
SPI_PICO11: J59.17, U47.25
SPI_POCI: J2.16, U1.24
SPI_POCI1: J9.16, U6.24
SPI_POCI2: J14.16, U11.24
SPI_POCI3: J19.16, U15.24
SPI_POCI4: J24.16, U19.24
SPI_POCI5: J29.16, U23.24
SPI_POCI6: J34.16, U27.24
SPI_POCI7: J39.16, U31.24
SPI_POCI8: J44.16, U35.24
SPI_POCI9: J49.16, U39.24
SPI_POCI10: J54.16, U43.24
SPI_POCI11: J59.16, U47.24
STAT_LED: D4.A, J2.5, U1.22
STAT_LED1: D8.A, J9.5, U6.22
STAT_LED2: D13.A, J14.5, U11.22
STAT_LED3: D18.A, J19.5, U15.22
STAT_LED4: D23.A, J24.5, U19.22
STAT_LED5: D28.A, J29.5, U23.22
STAT_LED6: D33.A, J34.5, U27.22
STAT_LED7: D38.A, J39.5, U31.22
STAT_LED8: D43.A, J44.5, U35.22
STAT_LED9: D48.A, J49.5, U39.22
STAT_LED10: D53.A, J54.5, U43.22
STAT_LED11: D58.A, J59.5, U47.22
TCLK: J7.4, U1.8
TCLK1: J10.4, U6.8
TCLK2: J15.4, U11.8
TCLK3: J20.4, U15.8
TCLK4: J25.4, U19.8
TCLK5: J30.4, U23.8
TCLK6: J35.4, U27.8
TCLK7: J40.4, U31.8
TCLK8: J45.4, U35.8
TCLK9: J50.4, U39.8
TCLK10: J55.4, U43.8
TCLK11: J60.4, U47.8
TMS: J7.2, TMS.1, U1.7
TMS1: J10.2, TMS1.1, U6.7
TMS2: J15.2, TMS2.1, U11.7
TMS3: J20.2, TMS3.1, U15.7
TMS4: J25.2, TMS4.1, U19.7
TMS5: J30.2, TMS5.1, U23.7
TMS6: J35.2, TMS6.1, U27.7
TMS7: J40.2, TMS7.1, U31.7
TMS8: J45.2, TMS8.1, U35.7
TMS9: J50.2, TMS9.1, U39.7
TMS10: J55.2, TMS10.1, U43.7
TMS11: J60.2, TMS11.1, U47.7
U0RXI: U1.13, U2.8
U0RXI1: U6.13, U8.8
U0RXI2: U11.13, U12.8
U0RXI3: U15.13, U16.8
U0RXI4: U19.13, U20.8
U0RXI5: U23.13, U24.8
U0RXI6: U27.13, U28.8
U0RXI7: U31.13, U32.8
U0RXI8: U35.13, U36.8
U0RXI9: U39.13, U40.8
U0RXI10: U43.13, U44.8
U0RXI11: U47.13, U48.8
U0TXO: U1.12, U2.9
U0TXO1: U6.12, U8.9
U0TXO2: U11.12, U12.9
U0TXO3: U15.12, U16.9
U0TXO4: U19.12, U20.9
U0TXO5: U23.12, U24.9
U0TXO6: U27.12, U28.9
U0TXO7: U31.12, U32.9
U0TXO8: U35.12, U36.9
U0TXO9: U39.12, U40.9
U0TXO10: U43.12, U44.9
U0TXO11: U47.12, U48.9
U1RXI: J2.15, U1.28
U1RXI1: J9.15, U6.28
U1RXI2: J14.15, U11.28
U1RXI3: J19.15, U15.28
U1RXI4: J24.15, U19.28
U1RXI5: J29.15, U23.28
U1RXI6: J34.15, U27.28
U1RXI7: J39.15, U31.28
U1RXI8: J44.15, U35.28
U1RXI9: J49.15, U39.28
U1RXI10: J54.15, U43.28
U1RXI11: J59.15, U47.28
U1TXO: J2.14, U1.29
U1TXO1: J9.14, U6.29
U1TXO2: J14.14, U11.29
U1TXO3: J19.14, U15.29
U1TXO4: J24.14, U19.29
U1TXO5: J29.14, U23.29
U1TXO6: J34.14, U27.29
U1TXO7: J39.14, U31.29
U1TXO8: J44.14, U35.29
U1TXO9: J49.14, U39.29
U1TXO10: J54.14, U43.29
U1TXO11: J59.14, U47.29
V_BATT: C10.1, J2.12, J4.2, Q1.3, U3.3
V_BATT1: C11.1, J6.2, J9.12, Q2.3, U5.3
V_BATT2: C18.1, J12.2, J14.12, Q3.3, U10.3
V_BATT3: C25.1, J17.2, J19.12, Q4.3, U14.3
V_BATT4: C32.1, J22.2, J24.12, Q5.3, U18.3
V_BATT5: C39.1, J27.2, J29.12, Q6.3, U22.3
V_BATT6: C46.1, J32.2, J34.12, Q7.3, U26.3
V_BATT7: C53.1, J37.2, J39.12, Q8.3, U30.3
V_BATT8: C60.1, J42.2, J44.12, Q9.3, U34.3
V_BATT9: C67.1, J47.2, J49.12, Q10.3, U38.3
V_BATT10: C74.1, J52.2, J54.12, Q11.3, U42.3
V_BATT11: C81.1, J57.2, J59.12, Q12.3, U46.3
V_USB: C7.1, CHG_LED.2, D2.A, D5.5, J2.10, J5.VBUS1, J5.VBUS2, R15.2, R18.1, U3.4
V_USB1: C6.1, CHG_LED1.2, D6.A, D10.5, J8.VBUS1, J8.VBUS2, J9.10, R23.2, R35.1, U5.4
V_USB2: C17.1, CHG_LED2.2, D11.A, D15.5, J13.VBUS1, J13.VBUS2, J14.10, R41.2, R53.1, U10.4
V_USB3: C24.1, CHG_LED3.2, D16.A, D20.5, J18.VBUS1, J18.VBUS2, J19.10, R59.2, R71.1, U14.4
V_USB4: C31.1, CHG_LED4.2, D21.A, D25.5, J23.VBUS1, J23.VBUS2, J24.10, R77.2, R89.1, U18.4
V_USB5: C38.1, CHG_LED5.2, D26.A, D30.5, J28.VBUS1, J28.VBUS2, J29.10, R95.2, R107.1, U22.4
V_USB6: C45.1, CHG_LED6.2, D31.A, D35.5, J33.VBUS1, J33.VBUS2, J34.10, R113.2, R125.1, U26.4
V_USB7: C52.1, CHG_LED7.2, D36.A, D40.5, J38.VBUS1, J38.VBUS2, J39.10, R131.2, R143.1, U30.4
V_USB8: C59.1, CHG_LED8.2, D41.A, D45.5, J43.VBUS1, J43.VBUS2, J44.10, R149.2, R161.1, U34.4
V_USB9: C66.1, CHG_LED9.2, D46.A, D50.5, J48.VBUS1, J48.VBUS2, J49.10, R167.2, R179.1, U38.4
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
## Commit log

2022-03-15 First hardware commit
    * Added datasheet and DA16200 eagle library
    * Starting from the RP2040 thing plus design files
2022-03-29 Working on initial design
    * Schematic almost done
    * Laying-out parts
2022-03-29 Working on schematic
2022-03-29 Pete's schematic suggestions
    * Add jumper to disable PWR LED
    * TVS protection for D+/D- lines
    * Add low value resistor (200) on reset line
    * multiple charge current options
    * Add 100 ohm between gate of Q2 and V_USB
2022-03-29 Switch pins around
2022-03-31 Eric's suggestions
    * Add external flash
    * Add a jumper to measure current draw
2022-03-31 Add documentation
2022-03-31 Routing
2022-04-02 Buzzard
2022-04-04 More buzzard
2022-04-04 Checklist
2022-04-05 Design review
2022-04-05 Design review updates
    Schematic:
    * Re-wire wakeup pins to match app schematic and previous designs
    * Change SHLD jumper to NC
    * Remove "ANT_GND" pin label from DA16200 symbol
    Board:
    * Draw polygon to connect shield pins of USBC connector on top and bottom
2022-04-05 QC Double-check updates
    * CURR jumper to MEAS
    * Move TPs onto 0.1 grid
    * line up LEDs
2022-04-12 Approve overlap errors on DRC
2022-04-12 Add GND vias to board
2022-04-12 Generate gerbers for proto (single board)
2022-04-12 Updated a few parts
2022-04-19 Fix some names on schematic
2022-04-29 Add EVK schematics to repo for reference
2022-05-09 Move LiPo, JTAG connector, and MEAS jumper to make room for connectors.
2022-05-10 Add "DNP" to external QSPI flash circuitry
2022-05-17 Updates for Red's
    * Added a NC jumper on the RTC_PWR_KEY pin to default to 3.3V. Users can cut the jumper to enter into sleep mode 1
2022-05-20 Remove external flash!
    The "F" pins are the pins internally connecting the DA16200 with the in-module 4MB SFLASH!
2022-05-20 Add SPDT switch for RTC_PWR_KEY
    Added surface mount switch to pull RTC_PWR_KEY to 3.3V or GND
    * Needed to extend the length of board by one grid space
2022-05-20 Add uSD friction fit to schematic
    * Renamed net labels to match connecting to the uSD socket defined by UM-WI-046 pg 30
2022-05-25 Add charge LED jumper
    Add charge LED jumper
2022-05-27 Update AP2112K to XC6222B33
2022-05-27 Update measures
2022-05-27 Add jumper to remove 3.3V from CH340E
2022-05-31 Change "IOC7" label to "IOA7" text
2022-05-31 Update logic analyzer data
2022-06-03 Remove SD card socket from design
2022-06-06 Approve DRC errors and remove wire stub
2022-06-07 Design review updates
    Schematic:
    * Remove "Ohm" from R11/R12 value
    * Add schematic symbol for ground onto USB SHLD
    Board:
    * set layers in order
    * Fix polygons to line up in DA16200 keep out area
2022-06-08 Design review updates
    Change DRC to 4 layer minimum rules, lots of little updates to avoid overlap. Annular ring size increased
2022-06-08 Fixing buzzard labels
2022-06-09 finish adding buzzard labels
2022-06-09 Design review updates
    * MEAS trace flipped to the bottom
    * Move components from bottom of board to the top
2022-06-09 Run through engineering checklist
2022-06-09 Update back buzzard labels
    Pin labels should be rounded and call out GPIO it's connected to
2022-06-09 Remove extra gerbers
2022-06-09 Panelize
2022-06-10 Some buzzard updates
    * Remove confusing labeling
    * Switch 3V3 and GND labels on SPDT switch because they were backwards
2022-06-10 re-panelize
2022-06-10 Final panel
    Kasey generated and approved!
2022-06-10 Create zip folder of .brd and .sch files
2022-06-16 Update README.md
    Added product information
    - product image link still needed
2022-06-16 Update README.md
    Remove div well
2022-07-28 Fix funky behaviors
    Add 0.1uF filter cap to DA16200
    Add 10k pullup to reset line
2022-07-28 Bump version number to v11
2022-07-28 Update production files
2022-07-28 Design review updates
    Add extra 0.1uF cap near VDD_DIO2
    Add NC jumper near SCLK pad to optionally remove pullup resistor and reset button
2022-09-13 Add dimensions
    Add board dimensions
2022-09-13 Renamed file
    add schematic to be more descriptive
2022-09-13 Updated files
    Includes revisions
    - pull-up resistor
    - added filter caps
    - reset jumper
    Added board dimensions
2022-09-14 rename and move board files
2022-09-14 move datasheet and guides
    removed guides that require user account to access
2022-09-15 add datasheets and guide
2022-09-15 Update README.md
    Add product image and update content info
2022-09-30 rename folder
2022-09-30 Add prebuilt firmware
    Add prebuilt firmware files
    - built with SDK v3.2.4.0
2022-09-30 add files for hookup guides
    add images for hookup guide and sdk guide
    add j-link files for sdk guide
